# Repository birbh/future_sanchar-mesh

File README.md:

# future_sanchar-jaal

Future_sanchar-jaal is a custom, open-source digital walkie-talkie powered by ESP32-S3. Unlike traditional analog radios those suffer from static or require a central router to work, this device uses the ESP-NOW v2 protocol to create a direct p2p 2.4GHz network. 

## What makes it unique??
It is unique because it used i2s components alongside a massive 1440 bytes transmission buffer which helps to deliver a crisp voice with an ultra-low latency. Also it uses esp32-S3-wroom-1u which has ipex antenna connector in it which has drastically helped to increase the range of walkie talkie. It provides upto 800+ meters range under normal conditions and if with obstacles it provides upto 200 meters range. 

## Why I made it??

Recently my country Nepal suffered a devastating flood which ruined so many human lives. So I thought that if I could make a Lo-Ra walkie-talkie, I could warn the people using the walkie-talkie along the long distance. Also in Nepal, due to difficult geography, the cellular network coverage could be unreliable when trekking and traveling through rural areas. In conclusion, I made this walkie-talkie to solve the real-world problem and help communicate over long distances easily. 

## How to use it?
1. Turn on the slide switch on the front side of the walkie-talkie.
2. The LED will flash Blue when booting and OLED will display "Sanchar-Jaal Boot".
3. Once the screen displays "Talk!! I am Listening..", you are ready and connected to the network.
4. Then press and hold the Push to Talk button in the front then the led will turn RED, and the screen will display "Transmitting.....!". Then you should speak near the microphone grill.
5. We will have paired devices, so when one talks the LED will turn GREEN and audio will automatically play through the speaker in front.
6. If the walkie talkie glitches then there is reset button in the back why can press that to fix the walkie talkie.
7. If the battery finishes then you can charge it through usb c in the left of walkie talkie
8. You can adjust the volume also from the onboard potentiometer to make the desired volume.

## Assembly Instructions:
### 3d print enclosure:
- All cad files are provided in the github repo.
- there are 3 separate cad files to be printed top lid, bottom lid and the base.
- You should print those 3 files separately

### PCB & soldering:
- All required files are provided in Production folder inside pcb_sanchar.
- solder all the smd components first as indicated in silkscreen
- then solder the usb-c breakout board to its assembly place in the left of walkie talkie using a wire i.e connect In+ and In- of tp4056 to the breakout board VBUS and GND respectively.
- then secure all the components in their respective mounts as in CAD. 

### Flashing firmware:
- Connect your FDTI adapter to J1 programming header on the board.
- Open the firmware file in the arduino ide.
- Hit upload -- when the console says connecting hold the BOOT button in the pcb and Press and release the RESET button then release the boot button.
- Wait for upload to finish then press BOOT button to boot the device.
- Then to pair the two devices check the serial monitor and find the MAC-address of DEVICE 1 and paste it into the code for DEVICE 2 (and vice versa). 

## Assets:
### Cad Screenshots:

### CAD link:
fusion360 ::: [Sanchar-jaal-cad](https://a360.co/4xBj2PT)

### Pcb:

### Schematic:

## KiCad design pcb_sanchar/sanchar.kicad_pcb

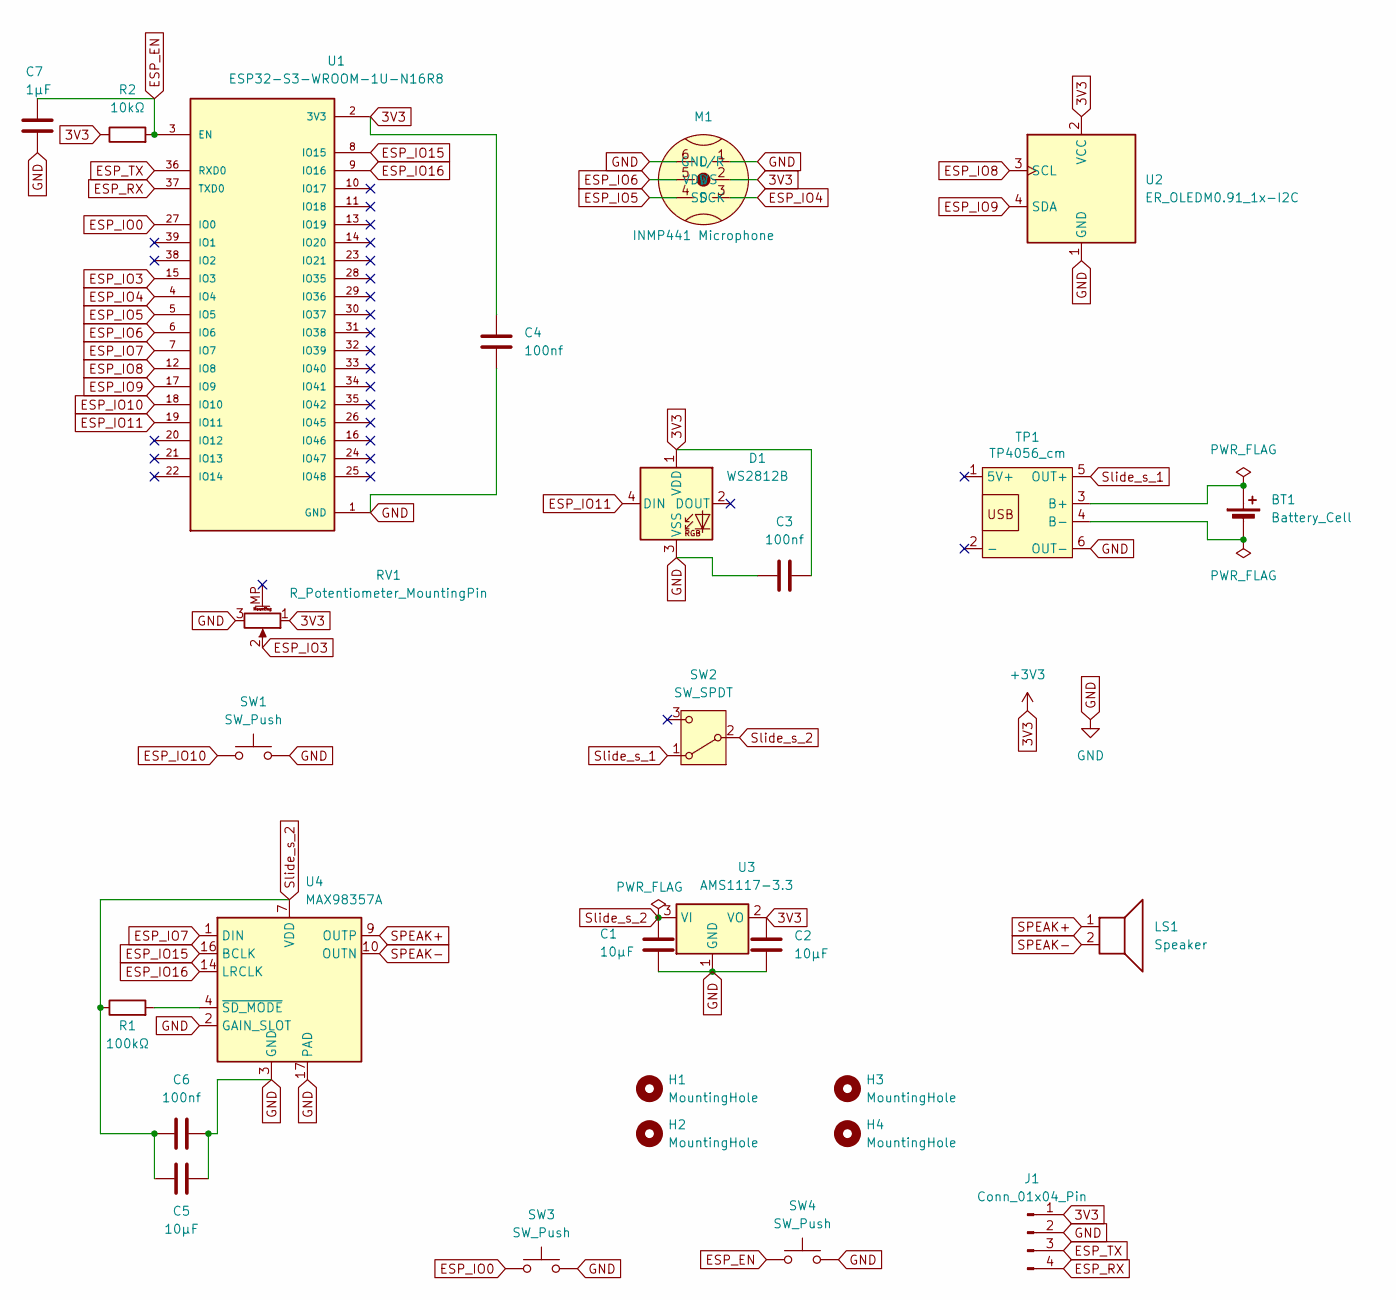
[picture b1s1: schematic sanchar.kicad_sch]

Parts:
BT1: Battery_Cell; JST_PH_S2B-PH-K_1x02_P2.00mm_Horizontal
C1, C2, C5: 10µF; C_0805_2012Metric
C3, C4, C6: 100nf; C_0805_2012Metric
C7: 1µF; C_0805_2012Metric
D1: WS2812B; LED_WS2812B_PLCC4_5.0x5.0mm_P3.2mm
H1, H2, H3, H4: MountingHole; MountingHole_3.2mm_M3
J1: Conn_01x04_Pin; FanPinHeader_1x04_P2.54mm_Vertical
LS1: Speaker; JST_PH_S2B-PH-K_1x02_P2.00mm_Horizontal
M1: INMP441 Microphone; INMP441_OMNIDIRECTIONAL_MICROPHONE_MODULE
R1: 100kΩ; R_0805_2012Metric
R2: 10kΩ; R_0805_2012Metric
RV1: R_Potentiometer_MountingPin; Potentiometer_Bourns_PTV09A-1_Single_Vertical
SW1, SW3, SW4: SW_Push; SW_Push_1P1T_NO_E-Switch_TL3301NxxxxxG
SW2: SW_SPDT; SW_Slide_SPDT_Straight_CK_OS102011MS2Q
TP1: TP4056_cm; TP4056-18650
U1: ESP32-S3-WROOM-1U-N16R8; XCVR_ESP32-S3-WROOM-1U-N16R8; PARTREV v1.1
U2: ER_OLEDM0.91_1x-I2C
U3: AMS1117-3.3; SOT-223-3_TabPin2
U4: MAX98357A; TQFN-16-1EP_3x3mm_P0.5mm_EP1.23x1.23mm

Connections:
3V3: C2.1, C3.2, C4.1, D1.1 (VDD), J1.1, M1.2 (VDD), R2.1, RV1.1, U1.2 (3V3), U2.2 (VCC), U3.2 (VO)
ESP_EN: C7.1, R2.2, SW4.1, U1.3 (EN); also elsewhere on the board
ESP_IO0: SW3.1, U1.27 (IO0); also elsewhere on the board
ESP_IO3: RV1.2, U1.15 (IO3)
ESP_IO4: M1.3 (SD), U1.4 (IO4)
ESP_IO5: M1.4 (SCK), U1.5 (IO5)
ESP_IO6: M1.5 (WS), U1.6 (IO6)
ESP_IO7: U1.7 (IO7), U4.1 (DIN)
ESP_IO8: U1.12 (IO8), U2.3 (SCL)
ESP_IO9: U1.17 (IO9), U2.4 (SDA)
ESP_IO10: SW1.1, U1.18 (IO10)
ESP_IO11: D1.4 (DIN), U1.19 (IO11)
ESP_IO15: U1.8 (IO15), U4.16 (BCLK)
ESP_IO16: U1.9 (IO16), U4.14 (LRCLK)
ESP_RX: J1.4, U1.37 (TXD0)
ESP_TX: J1.3, U1.36 (RXD0)
GND: C1.2, C2.2, C3.1, C4.2, C5.2, C6.2, C7.2, D1.3 (VSS), J1.2, M1.1 (GND), M1.6 (L/R), RV1.3, SW1.2, SW3.2, SW4.2, TP1.6 (OUT-), U1.1 (GND), U1.40 (GND), U1.41_1 (GND), U1.41_2 (GND), U1.41_3 (GND), U1.41_4 (GND), U1.41_5 (GND), U1.41_6 (GND), U1.41_7 (GND), U1.41_8 (GND), U1.41_9 (GND), U1.41_10, U1.41_11, U1.41_12, U1.41_13, U1.41_14, U1.41_15, U1.41_16, U1.41_17, U1.41_18, U1.41_19, U1.41_20, U1.41_21, U2.1 (GND), U3.1 (GND), U4.2 (GAIN_SLOT), U4.3 (GND), U4.11 (GND), U4.15 (GND), U4.17 (PAD); also elsewhere on the board
unnamed: BT1.1 (+), TP1.3 (B+)
unnamed: BT1.2 (-), TP1.4 (B-)
unnamed: R1.2, U4.4 (~SD_MODE)
SPEAK+: LS1.1, U4.9 (OUTP)
SPEAK-: LS1.2, U4.10 (OUTN)
Slide_s_1: SW2.1 (A), TP1.5 (OUT+)
Slide_s_2: C1.1, C5.1, C6.1, R1.1, SW2.2 (B), U3.3 (VI), U4.7 (VDD), U4.8 (VDD)

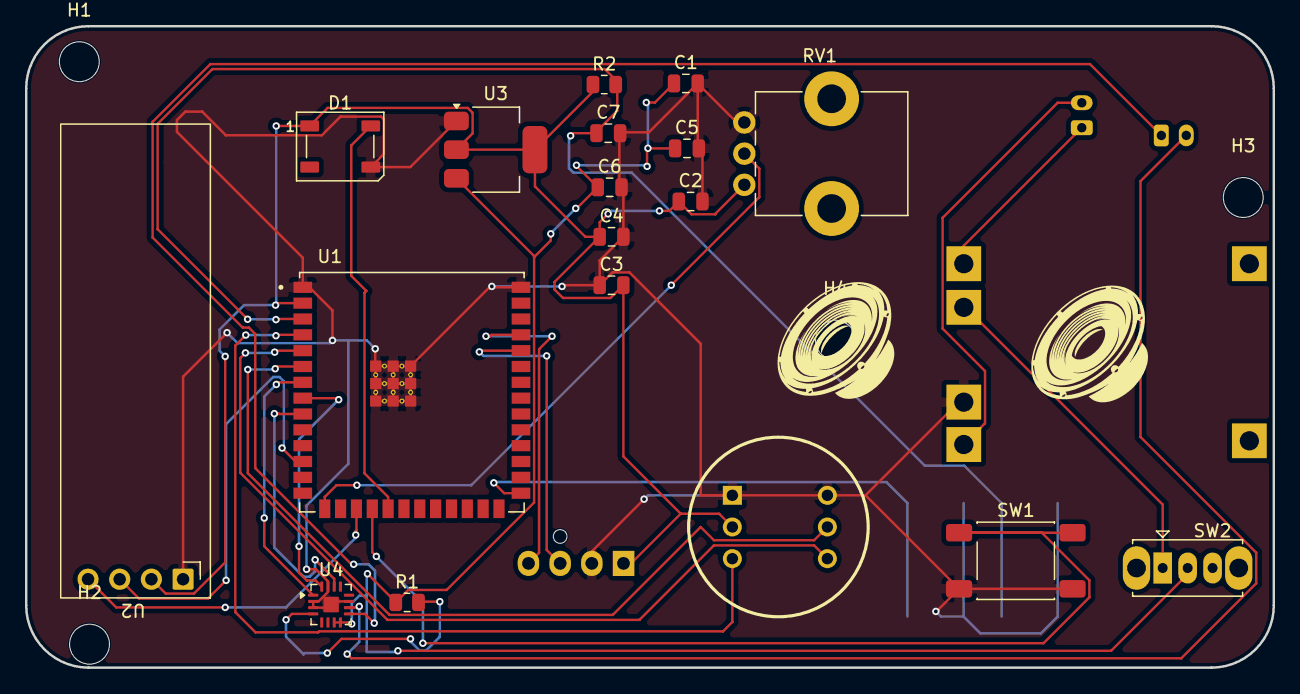
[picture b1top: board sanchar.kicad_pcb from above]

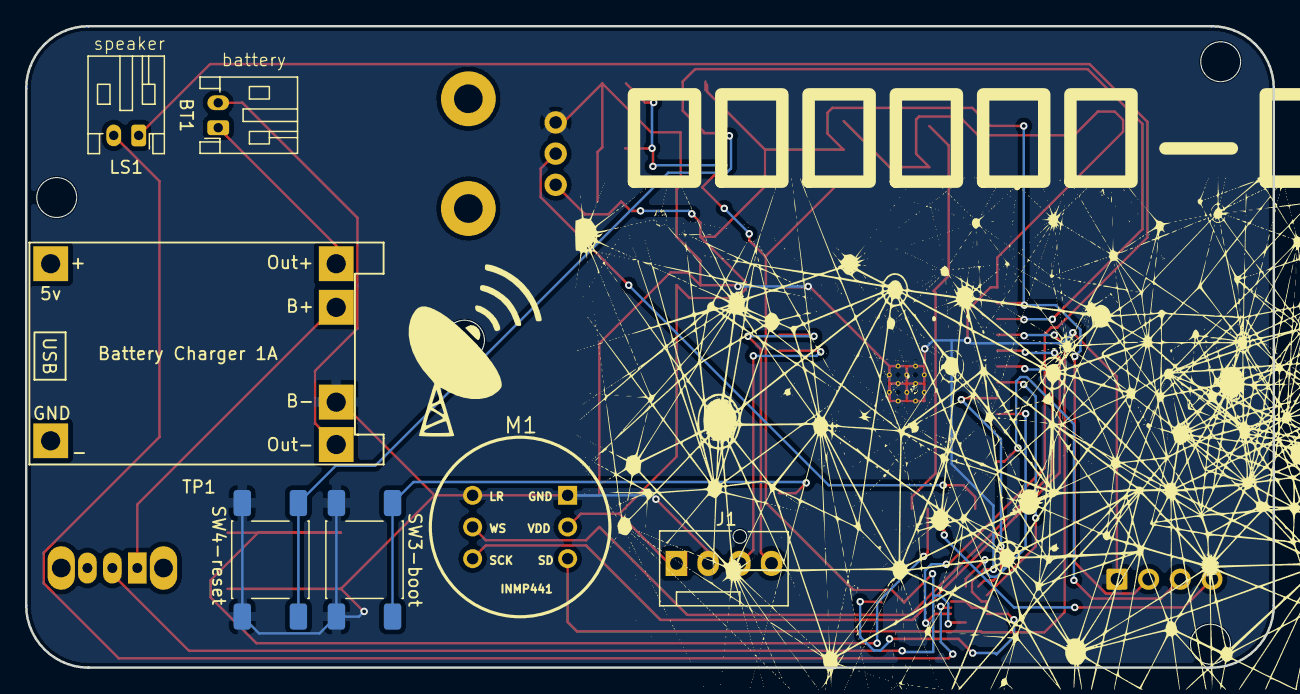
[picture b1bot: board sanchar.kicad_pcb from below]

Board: 2 copper layers, 100.1 x 51.4 mm, 28 parts (7 on the bottom side), 24 nets.

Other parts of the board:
SW3-boot, SW4-reset: SW_Push; SW_Push_1P1T_NO_E-Switch_TL3301NxxxxxG

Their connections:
ESP_EN: SW4-reset.1; also elsewhere on the board
ESP_IO0: SW3-boot.1; also elsewhere on the board
GND: SW3-boot.2, SW4-reset.2; also elsewhere on the board

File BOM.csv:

"Id";"Designator";"Footprint";"Quantity";"Designation";"Link";Price
1;"BT1";"JST_PH_S2B-PH-K_1x02_P2.00mm_Horizontal";4;"Battery_Cell";https://shorturl.at/hIcLj;$18
2;"C1, C2, C5";"C_0805_2012Metric";6;"10µF";https://shorturl.at/dkd7K;$2.3
3;"C3, C4, C6";"C_0805_2012Metric";6;"100nf";https://shorturl.at/dkd7K;$2.3
4;"C7";"C_0805_2012Metric";2;"1µF";https://shorturl.at/dkd7K;$2.3
5;"D1";"LED_WS2812B_PLCC4_5.0x5.0mm_P3.2mm";2;"WS2812B";https://shorturl.at/Q40h6;$11
6;"J1";"FanPinHeader_1x04_P2.54mm_Vertical";2;"Conn_01x04_Pin";https://shorturl.at/0AHKv;$7
7;"LS1";"JST_PH_S2B-PH-K_1x02_P2.00mm_Horizontal";2;"Speaker";https://shorturl.at/RXhoH;$5
8;"M1";"INMP441_OMNIDIRECTIONAL_MICROPHONE_MODULE";2;"INMP441 Microphone";https://h1.nu/1ydcw;$8
9;"R1";"R_0805_2012Metric";2;"100kΩ";https://h1.nu/1ydd0;$1
10;"R2";"R_0805_2012Metric";2;"10kΩ";https://h1.nu/1ydd0;$1
11;"RV1";"Potentiometer_Bourns_PTV09A-1_Single_Vertical";2;"R_Potentiometer_MountingPin";https://h1.nu/1yddz;$2.9
12;"SW1, SW3-boot, SW4-reset";"SW_Push_1P1T_NO_E-Switch_TL3301NxxxxxG";6;"SW_Push";https://h1.nu/1ydel;$9
13;"SW2";"SW_Slide_SPDT_Straight_CK_OS102011MS2Q";2;"SW_SPDT";https://h1.nu/1DZo9;$4.5
14;"TP1";"TP4056-18650";2;"TP4056_cm";https://h1.nu/1DZoD;$3.5
15;"U1";"XCVR_ESP32-S3-WROOM-1U-N16R8";2;"ESP32-S3-WROOM-1U-N16R8";https://h1.nu/1ydgw;$9.86
16;"U2";"ER_OLEDM0.91_1x-I2C";2;"ER_OLEDM0.91_1x-I2C";https://h1.nu/1ydh5;$6.88
17;"U3";"SOT-223-3_TabPin2";2;"AMS1117-3.3";https://h1.nu/1DZr0;$6
18;"U4";"TQFN-16-1EP_3x3mm_P0.5mm_EP1.23x1.23mm";2;"MAX98357A";https://h1.nu/1ydjG;$2.65
19;;;2;"USB Type C Connector
Board 3.1 Serial Basic Breakout Female";https://h1.nu/1DZtC;$4.99
20;;;2;JST_PH;https://h1.nu/1DZvK;$.24
;TOTAL;;;;;$108.42
